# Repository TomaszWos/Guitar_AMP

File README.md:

# Guitar_AMP
Projekt wzmacniacza lampowego do domowego użytku. 
Podczas projektowania korzystałem ze schematów kultowych konstrukcji takich firm jak Marshall, Fender czy Engl.
Schematy dostępne na https://el34world.com/.

**VER_1** 

Pierwsza wersja wzmacniacza została oparta na schemacie AX84. 

Różnice występują jedynie w wartościach poszczególnych elementów.

Jest to jednokanałowy, lampowy wzmacniacz gitarowy. Układ przedwzmacniacza oparty jest na lampie ECC83 i inspirowany jest konstrukcjami Fendera.
Pozwala uzyskać klasyczne brzmienia od czystych do lekkiego chrunchu. Układ wzmacniacza mocy zbudowany został na EL84 w klasie A. Ponad to wzmacniacz posiada EQ, którego kostrukcja jest klasycznym trzystopniowe EQ jakie występowało w pierwszych wzmacniacza Fendera, Marshalla lub Voxa. 
Od nowa zostały policzone wartości napięć w układzie zasilającym oraz napięcia biasu poszczególnych katod lamp.
Układ jest podstawą do dalszych zmian i modyfikacji.

**VER_1.1**

Pierwsze modyfikacje zostały wprowadzone do układu przedwzmacniacza, tak aby rozszerzyć możliwości brzmieniowe wzmacniacza.
Została dodana druga lampa ECC83 w celu uzystania większego wzmocnienia i większej możliwości kształtowania brzmienia. Zmiana potencjometru GAIN na 1M zwiększyła wzmocnienie pierwszej triody, a co za tym idzie uzyskanie większego przesterowania.
Dodano drugi potencjometr GAIN za drugą triodą. Rozszerzono układ o drugi kanał o dużym przesterowaniu. Przełącznik SW1 służy do zmiany kanałów. Przester tworzy układ diod, które zaczynają przewodzić po osiągnięciu około napięcia 2V. Sygnał zostaje ścięty i kształtem jest zbliżony do prostokątnego. Kondensator 1n przepuszcza wysokie częstotliwości tak, aby dźwięk był mniej syczący. 
Rezystor na pierwszej katodzie zmieniono na 2.2k a kondensator na 680n. Sprawia to, że wyższe częstotliwości są bardziej wzmacniane niż niskie. Dodano kondensatory na torze sygnałowym tak, aby zwiększyć zawartość wyższych harmonicznych w sygnale. Brzmienie jest znacznie jaśniejsze i bardziej szkliste na wzór wzmacniaczy Marshall.

**VER_2**

W pełni lampowy wzmacniacz w klasie A z dwoma kanałami : Clean i Lead. Kanał Lead jest oparty na 4 triodach i jest stylizowany na wzmacniaczach typu Hi-Gain firmy ENGL.

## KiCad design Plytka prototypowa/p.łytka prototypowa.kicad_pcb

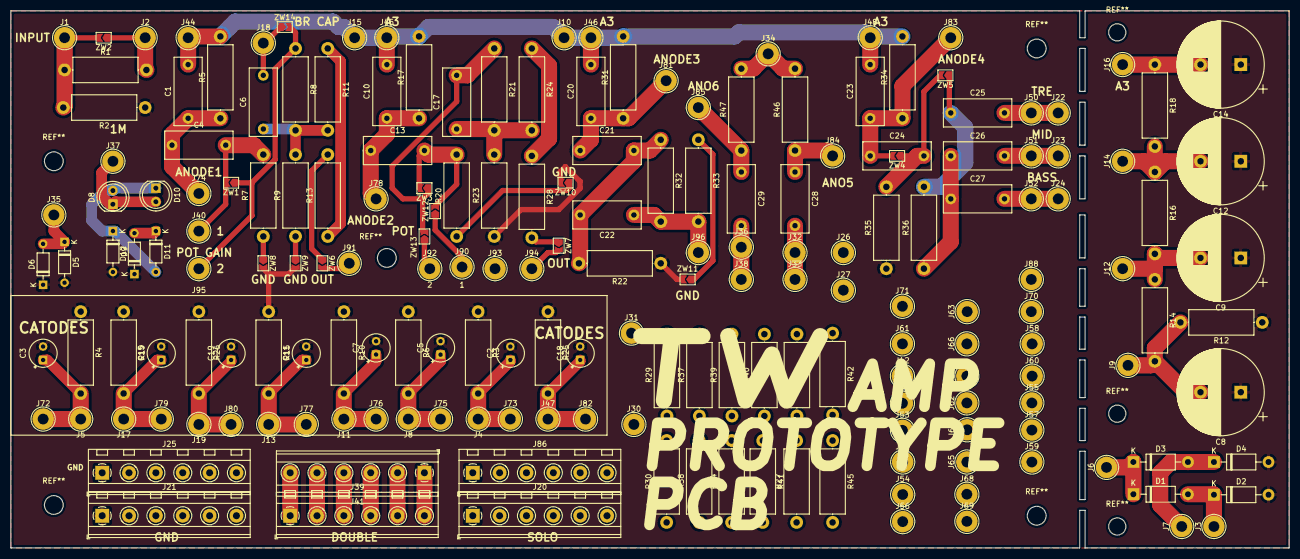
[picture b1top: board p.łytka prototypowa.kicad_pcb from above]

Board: 2 copper layers, 238.0 x 100.0 mm, 192 parts (0 on the bottom side), 65 nets.

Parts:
C1, C4, C6, C10, C13, C17, C20, C21, C22, C23, C24, C25, C26, C27, C28, C29: C; C_Disc_D12.5mm_W5.0mm_P10.00mm
C2, C3, C5, C7, C11, C15, C18, C19: C; CP_Radial_Tantal_D5.0mm_P2.50mm
C8, C9, C12, C14: C; CP_Radial_D16.0mm_P7.50mm
D1, D2, D3, D4: 1N4007; D_DO-41_SOD81_P10.16mm_Horizontal
D5, D6, D9, D11, D12: 1N4148; D_DO-35_SOD27_P7.62mm_Horizontal
D8, D10: LED; LED_D5.0mm
J1: INPUT; TestPoint_THTPad_D4.0mm_Drill2.0mm
J2: INPUT2; TestPoint_THTPad_D4.0mm_Drill2.0mm
J3, J7: AC; TestPoint_THTPad_D4.0mm_Drill2.0mm
J4, J5, J6, J8, J11, J13, J17, J18, J19, J26, J27, J30, J31, J32, J33, J34, J35, J36, J37, J38, J40, J42, J43, J44, J45, J46, J47, J48, J49, J50, J51, J52, J53, J54, J55, J56, J57, J58, J59, J60, J61, J62, J63, J64, J65, J66, J67, J68, J69, J70, J71, J72, J73, J74, J75, J76, J77, J78, J79, J80, J81, J82, J83, J84, J85, J88, J90, J91, J92, J93, J94, J95, J96: Conn_01x01_Male; TestPoint_THTPad_D4.0mm_Drill2.0mm
J9: IN POWER; TestPoint_THTPad_D4.0mm_Drill2.0mm
J10, J15, J16: A3; TestPoint_THTPad_D4.0mm_Drill2.0mm
J12: A1; TestPoint_THTPad_D4.0mm_Drill2.0mm
J14: A2; TestPoint_THTPad_D4.0mm_Drill2.0mm
J20, J86: LUŹNE; TerminalBlock_MetzConnect_Type094_RT03506HBLU_1x06_P5.00mm_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
J21: MASA; TerminalBlock_MetzConnect_Type094_RT03506HBLU_1x06_P5.00mm_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
J22: Treble; TestPoint_THTPad_D4.0mm_Drill2.0mm
J23: MID; TestPoint_THTPad_D4.0mm_Drill2.0mm
J24: Bass; TestPoint_THTPad_D4.0mm_Drill2.0mm
J25: MASA2; TerminalBlock_MetzConnect_Type094_RT03506HBLU_1x06_P5.00mm_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
J39: Conn_01x06_Male; TerminalBlock_MetzConnect_Type094_RT03506HBLU_1x06_P5.00mm_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
J41: LUŹNE2; TerminalBlock_MetzConnect_Type094_RT03506HBLU_1x06_P5.00mm_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
R1, R3, R4, R5, R6, R7, R8, R9, R10, R11, R12, R13, R14, R15, R16, R17, R18, R19, R20, R21, R22, R23, R24, R25, R26, R27, R28, R29, R30, R31, R32, R33, R34, R35, R36, R37, R38, R39, R40, R41, R42, R43, R44, R45, R46, R47: R; R_Axial_DIN0414_L11.9mm_D4.5mm_P15.24mm_Horizontal
R2: 1M; R_Axial_DIN0414_L11.9mm_D4.5mm_P15.24mm_Horizontal
ZW1, ZW2, ZW3, ZW4, ZW5, ZW6, ZW7, ZW8, ZW9, ZW10, ZW11, ZW12, ZW13, ZW14: R; SolderJumper-2_P1.3mm_Open_TrianglePad1.0x1.5mm

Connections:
GND: C2.2, C3.2, C5.2, C7.2, C8.1, C9.1, C11.2, C12.1, C14.1, C15.2, C18.2, C19.2, D2.2, D4.2, D5.2, D6.1, D9.2, D12.1, J21.1, J21.2, J21.3, J21.4, J21.5, J21.6, J25.1, J25.2, J25.3, J25.4, J25.5, J25.6, R2.1, R3.1, R4.1, R6.1, R10.1, R12.1, R15.1, R19.1, R22.1, R23.1, R25.1, R26.1, R35.1, ZW8.2, ZW9.2, ZW10.2, ZW11.2
unnamed: C1.1, C4.1, J74.1, R5.1
unnamed: C1.2, C10.2, C20.2, C23.2, J10.1, J15.1, J44.1, J45.1, J46.1, J48.1, R5.2, R17.2, R31.2, R34.2
unnamed: C2.1, J4.1, J73.1, R3.2
unnamed: C3.1, J5.1, J72.1, R4.2
unnamed: C4.2, J40.1, R7.2, ZW1.2
unnamed: C5.1, J8.1, J75.1, R6.2
unnamed: C6.1, R8.2, R9.2, R11.2
unnamed: C6.2, J18.1, ZW14.1
unnamed: C7.1, J11.1, J76.1, R10.2
unnamed: C8.2, J9.1, R12.2, R14.2
unnamed: C9.2, J12.1, R14.1, R16.2
unnamed: C10.1, C13.1, J78.1, R17.1
unnamed: C11.1, J13.1, J77.1, R15.2
unnamed: C12.2, J14.1, R16.1, R18.2
unnamed: C13.2, R20.2, ZW3.2, ZW12.2
unnamed: C14.2, J16.1, R18.1
unnamed: C15.1, J17.1, J79.1, R19.2
unnamed: C17.1, R21.2, R23.2, R24.2
unnamed: C17.2, R21.1, ZW3.1, ZW13.2
unnamed: C18.1, J47.1, J82.1, R25.2
unnamed: C19.1, J19.1, J80.1, R26.2
unnamed: C20.1, C21.1, J81.1, R31.1
unnamed: C21.2, C22.2, R22.2, R32.1
unnamed: C22.1, J96.1, R32.2, R33.2
unnamed: C23.1, C24.1, J83.1, R34.1, ZW4.2
unnamed: C24.2, R35.2, ZW4.1, ZW5.2
unnamed: C25.1, R36.2, ZW5.1
unnamed: C25.2, J22.1, J50.1
unnamed: C26.1, C27.1, R36.1
unnamed: C26.2, J23.1, J51.1
unnamed: C27.2, J24.1, J52.1
unnamed: C28.1, J84.1, R46.1
unnamed: C28.2, J32.1, J33.1
unnamed: C29.1, J85.1, R47.1
unnamed: C29.2, J36.1, J38.1
unnamed: D1.1, D3.1, J6.1
unnamed: D1.2, D2.1, J3.1
unnamed: D3.2, D4.1, J7.1
unnamed: D5.1, D6.2, J35.1
unnamed: D8.2, D9.1, D10.1, D11.2
unnamed: D8.1, D10.2, J37.1
unnamed: D11.1, D12.2
unnamed: J1.1, R1.1, R2.2, ZW2.2
unnamed: J2.1, R1.2, ZW2.1
unnamed: J34.1, R46.2, R47.2
unnamed: J39.1, J41.6
unnamed: J39.2, J41.5
unnamed: J39.3, J41.4
unnamed: J39.4, J41.3
unnamed: J39.5, J41.2
unnamed: J39.6, J41.1
unnamed: J90.1, ZW12.1
unnamed: J91.1, ZW6.2
unnamed: J92.1, ZW13.1
unnamed: J94.1, ZW7.2
unnamed: J95.1, R8.1, ZW1.1, ZW14.2
unnamed: R7.1, ZW8.1
unnamed: R9.1, ZW9.1
unnamed: R11.1, R13.1
unnamed: R13.2, ZW6.1
unnamed: R20.1, ZW10.1
unnamed: R24.1, R28.1
unnamed: R28.2, ZW7.1
unnamed: R33.1, ZW11.1

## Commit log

2022-08-04 Create new
2022-08-04 Rename new to new.md
2023-02-22 Create a
2023-02-22 Create Opis
